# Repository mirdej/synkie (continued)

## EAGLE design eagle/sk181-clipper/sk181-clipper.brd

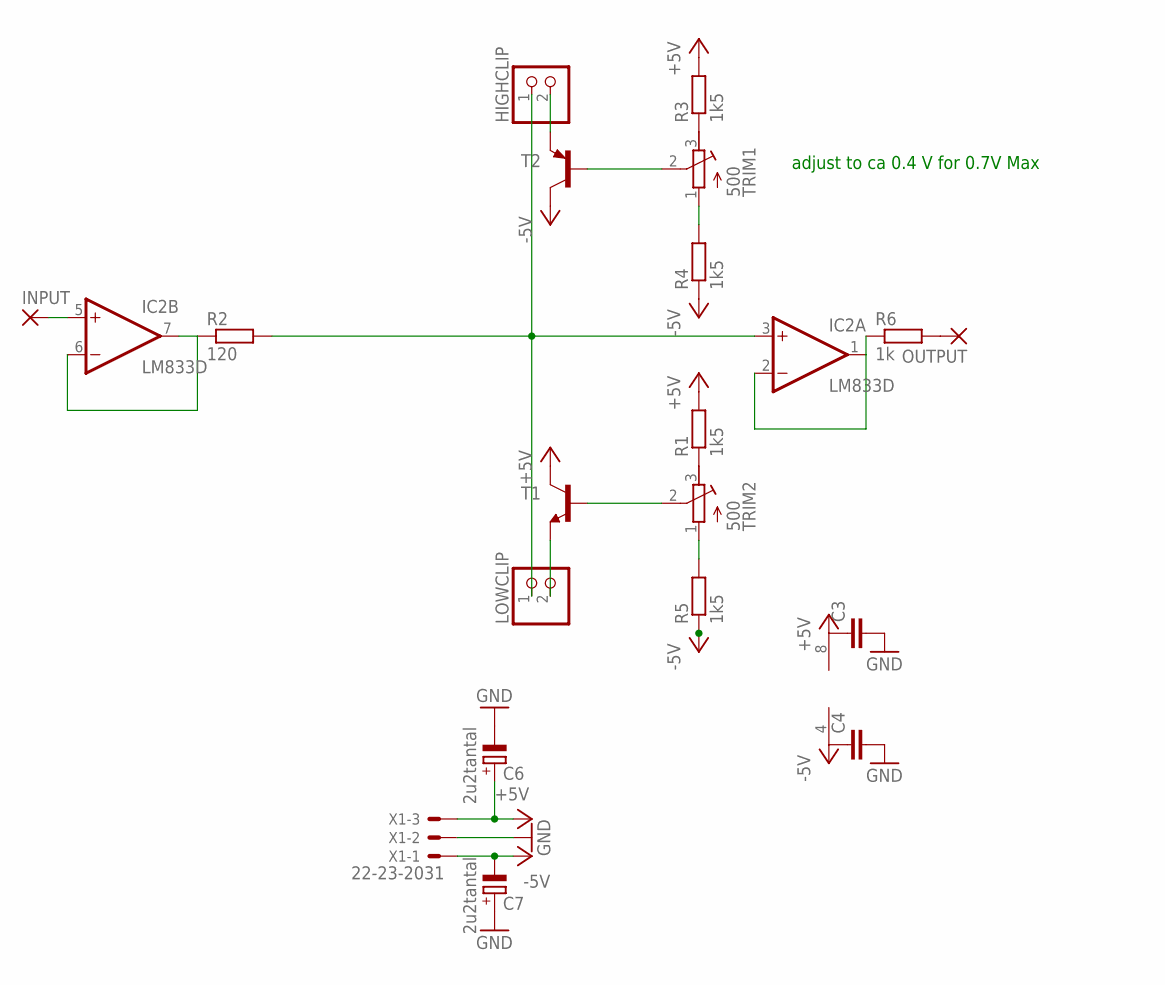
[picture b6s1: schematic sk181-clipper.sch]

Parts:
C3, C4: C-EUC0603; C0603
C6, C7: 2u2tantal; CT3528
HIGHCLIP: PINHD-1X2; 1X02
IC2: LM833D; SO08
INPUT: 3,17/1,1
LOWCLIP: PINHD-1X2; 1X02
OUTPUT: 3,17/1,1
R1, R3, R4, R5: 1k5; R1206
R2: 120; R1206
R6: 1k; R1206
T1: TRANS-NPN; SOT23-BEC
T2: TRANS-PNPSOT23-BEC; SOT23-BEC
TRIM1, TRIM2: 500; RTRIM64Y
X1: 22-23-2031

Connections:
+5V: C3.1, C6.+, IC2.8 (V+), R1.2, R3.2, T1.C, X1.3
-5V: C4.1, C7.-, IC2.4 (V-), R4.1, R5.1, T2.C, X1.1
GND: C3.2, C4.2, C6.-, C7.+, X1.2
unnamed: IC2.1 (OUT), IC2.2 (-IN), R6.1
unnamed: HIGHCLIP.1, IC2.3 (+IN), LOWCLIP.1, R2.2
unnamed: HIGHCLIP.2, T2.E
unnamed: R1.1, TRIM2.3 (A)
unnamed: R4.2, TRIM1.1 (E)
unnamed: T2.B, TRIM1.2 (S)
unnamed: R5.2, TRIM2.1 (E)
unnamed: R3.1, TRIM1.3 (A)
unnamed: LOWCLIP.2, T1.E
unnamed: OUTPUT.1, R6.2
unnamed: T1.B, TRIM2.2 (S)
unnamed: IC2.6 (-IN), IC2.7 (OUT), R2.1
unnamed: IC2.5 (+IN), INPUT.1

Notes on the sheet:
adjust to ca 0.4 V for 0.7V Max

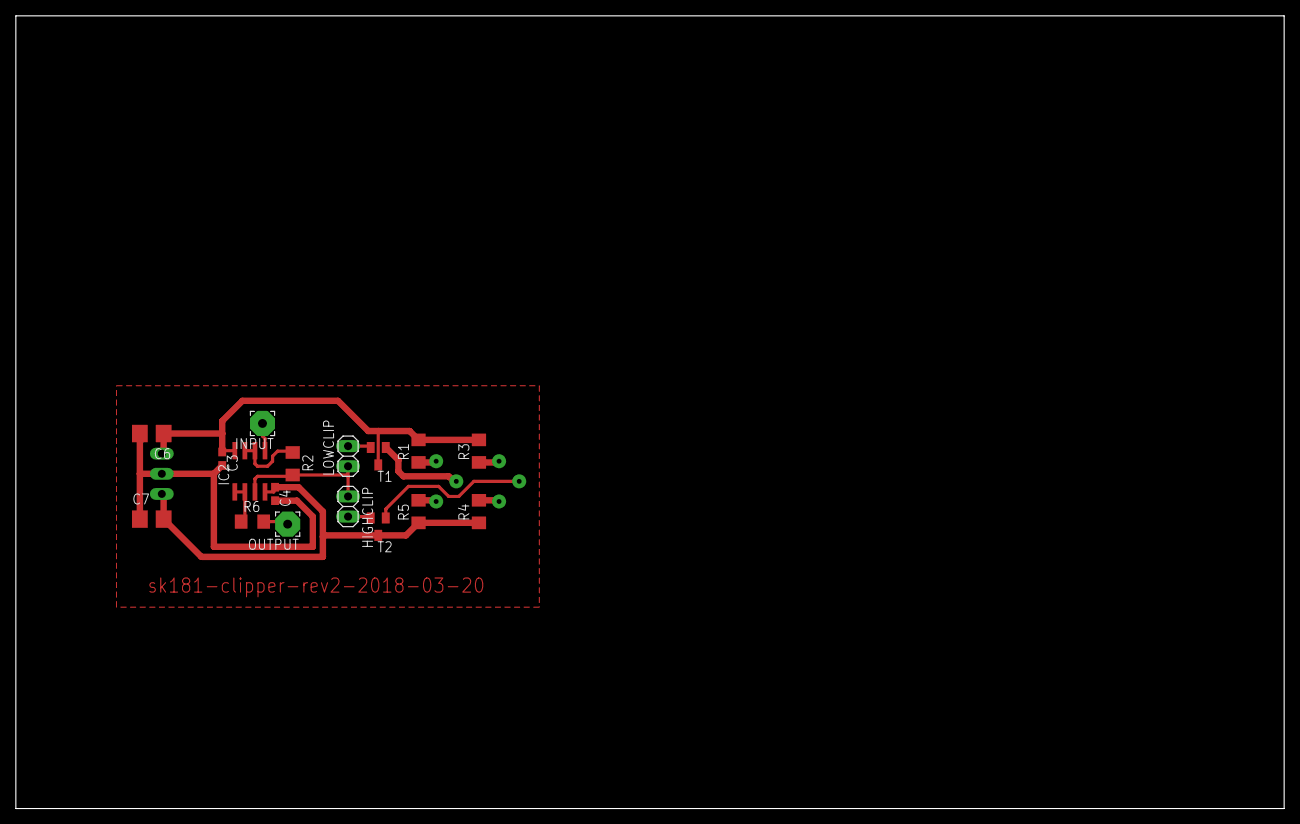
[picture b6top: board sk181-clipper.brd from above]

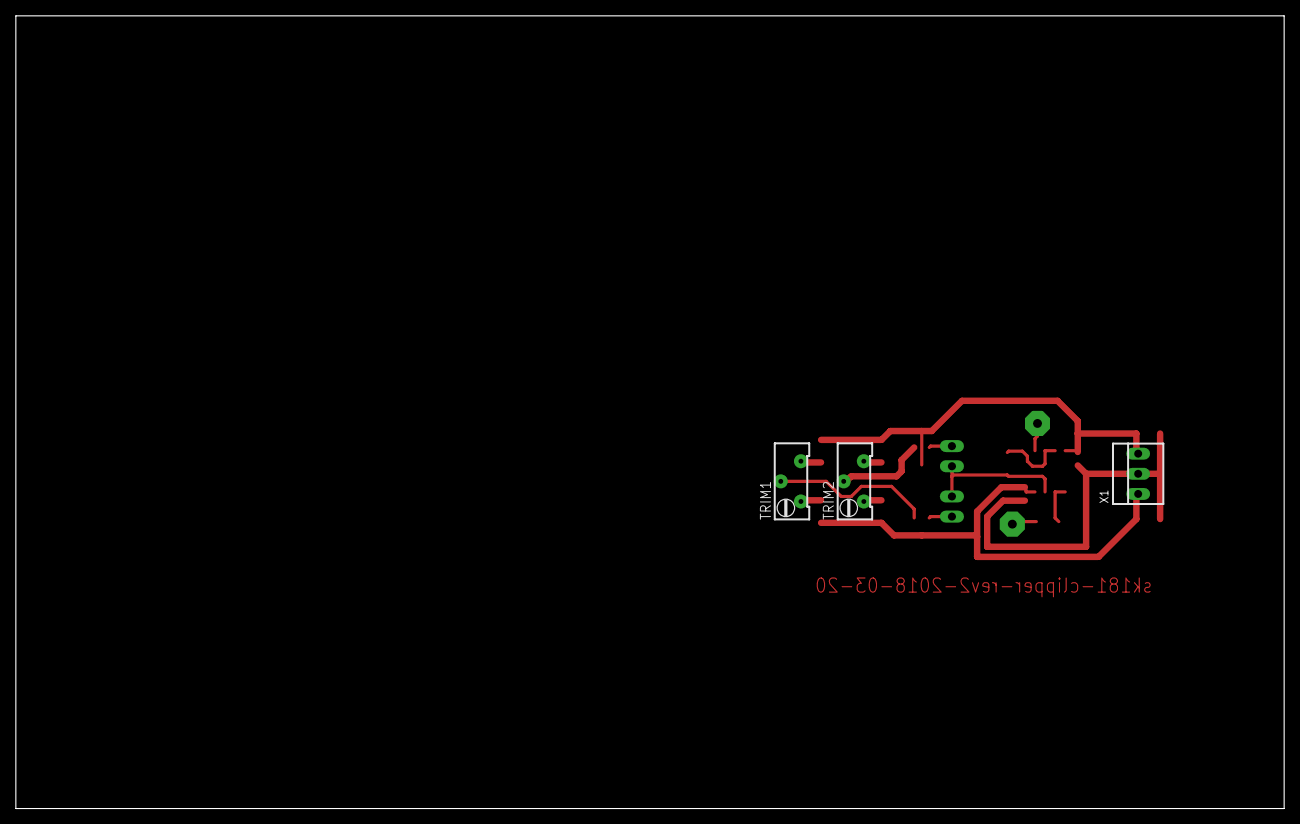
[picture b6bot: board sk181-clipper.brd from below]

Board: 2 copper layers, 160.0 x 100.0 mm, 20 parts (3 on the bottom side), 16 nets.
